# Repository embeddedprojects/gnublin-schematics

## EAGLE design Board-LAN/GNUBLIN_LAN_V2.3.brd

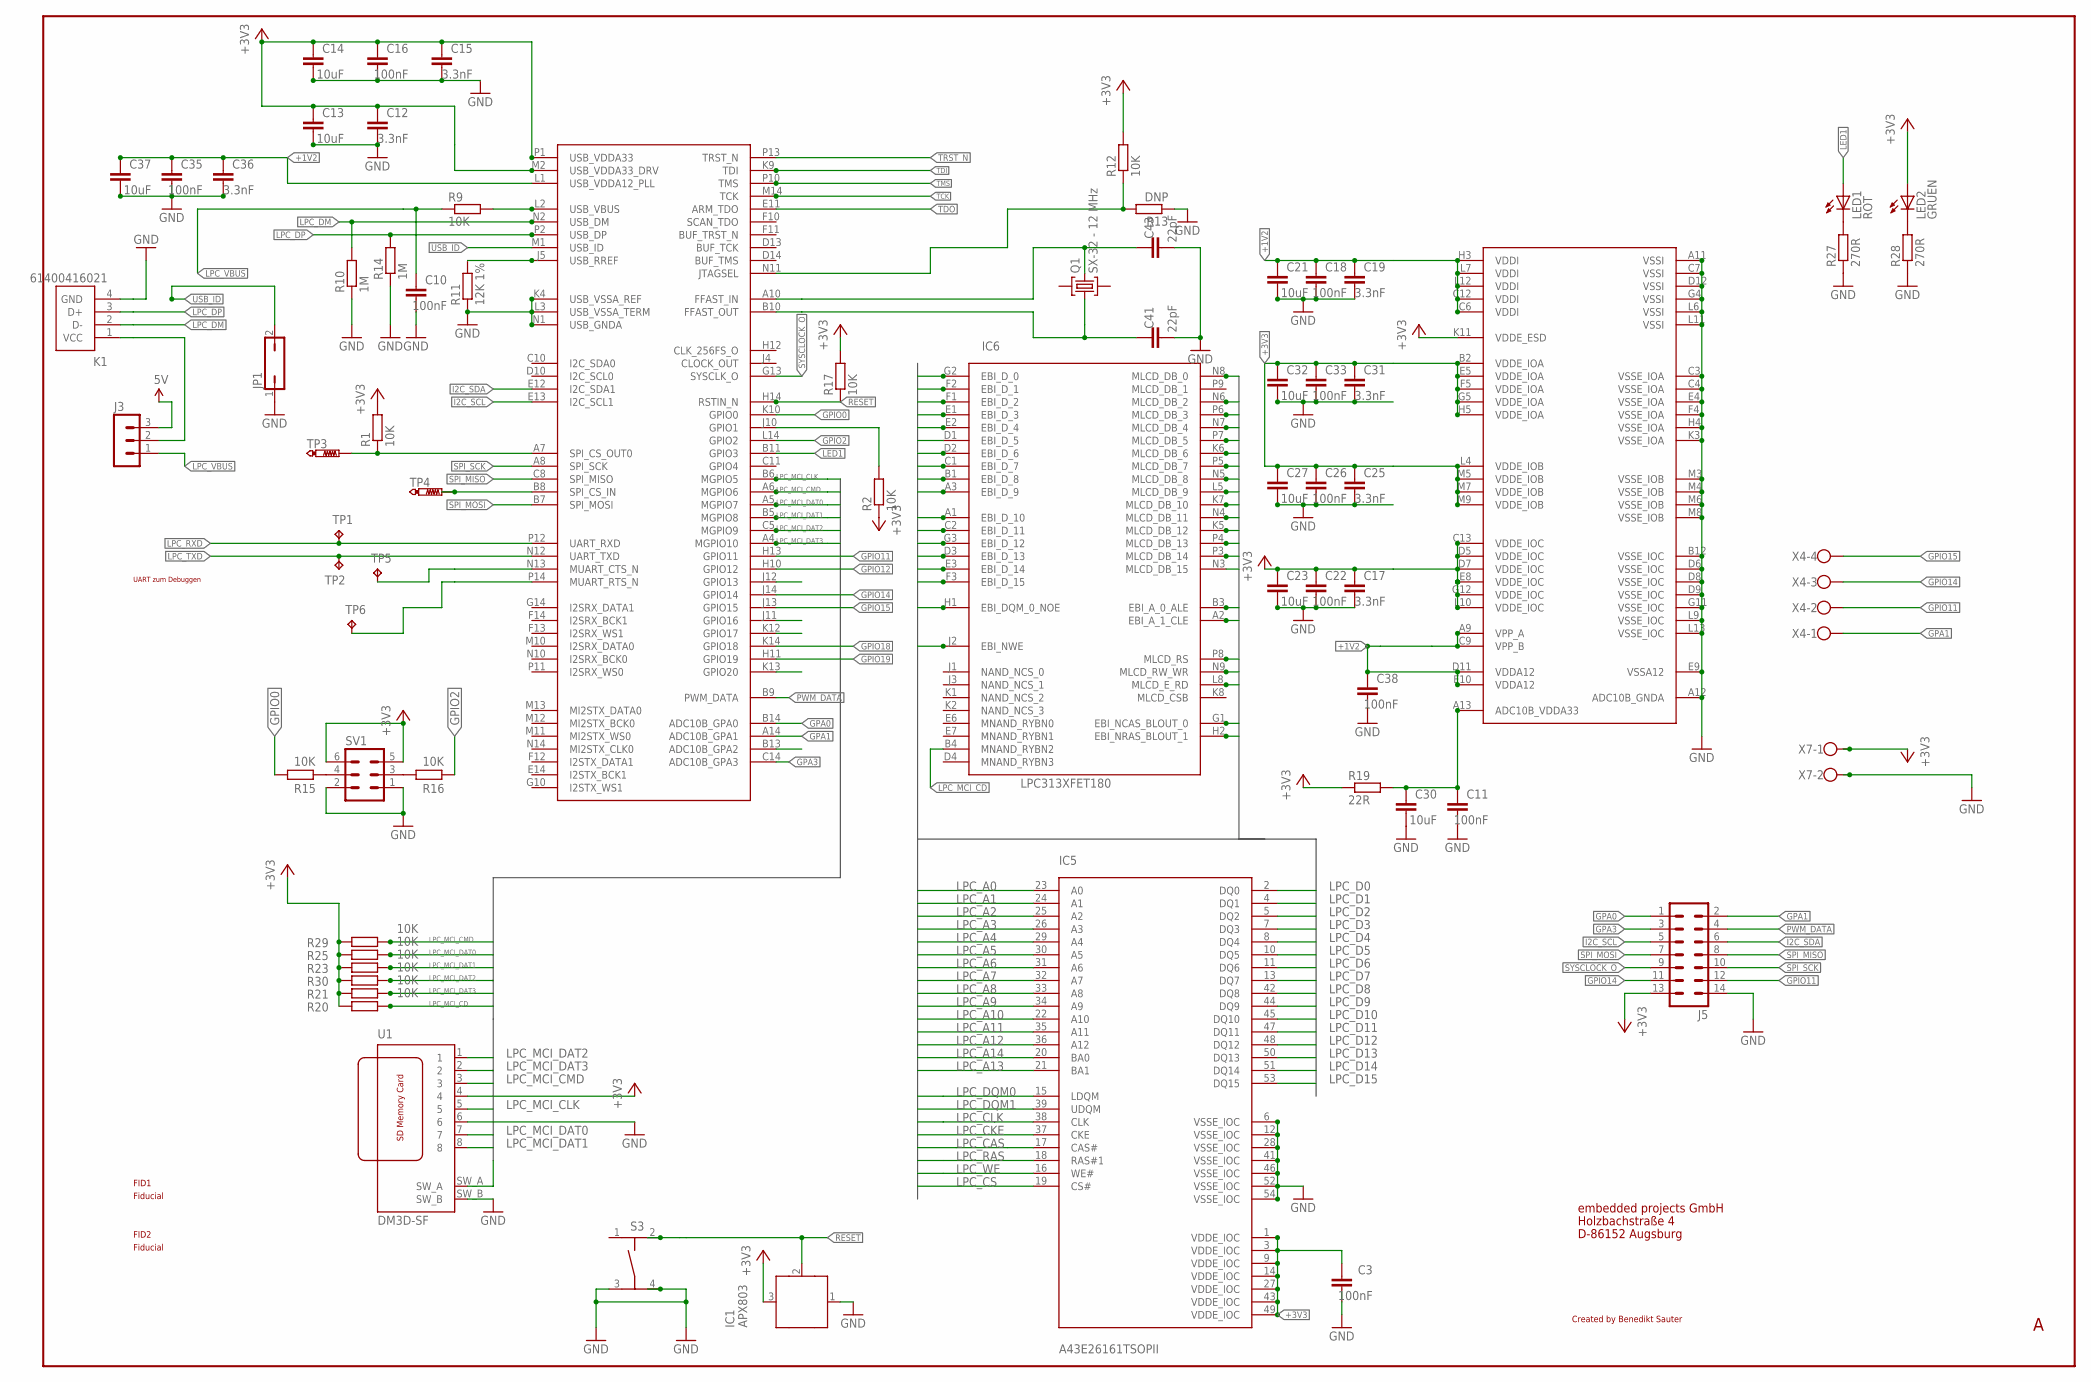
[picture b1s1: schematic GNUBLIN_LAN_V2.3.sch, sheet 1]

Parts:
C3, C10, C11, C16, C18, C22, C26, C33, C35, C38: 100nF; C0805
C12, C15, C17, C19, C25, C31, C36: 3.3nF; C0805
C13, C14, C21, C23, C27, C30, C32, C37: 10uF; C0805
C41, C43: 22pF; C0805
FID1, FID2: PASSERMARKEN_FIDUCIAL
IC1: APX803; SOT23
IC5: A43E26161TSOPII; TSOPII
IC6: LPC313XFET180; TFBGA180
J3: MA03-1
J5: ML14
JP1: JP1Q; JP1
K1: 61400416021
LED1: ROT; CHIP-LED0805
LED2: GRUEN; CHIP-LED0805
Q1: SX-32 - 12 MHz; SX-32; FARNELL 1712841
R1, R2, R9, R12, R15, R16, R17, R20, R21, R23, R25, R29, R30: 10K; R0805
R10, R14: 1M; R0805
R11: 12K 1%; R0805
R13: DNP; R0805
R19: 22R; R0805
R27, R28: 270R; R0805
S3: TASTER-9314_SMD
SV1: MA03-2
TP1, TP2: TPTP15R; TP15R
TP3, TP4: PTR1TP08R; TP08R
TP5, TP6: TPTP08R; TP08R
U1: DM3D-SF
X4: W237-04P; W237-4P
X7: W237-02P; W237-132

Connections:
5V: J3.3; also elsewhere on the board
+1V2: C18.2, C19.2, C21.2, C35.2, C36.2, C37.2, C38.2, IC6.A9 (VPP_A), IC6.C6 (VDDI), IC6.C9 (VPP_B), IC6.C12 (VDDI), IC6.D11 (VDDA12), IC6.E10 (VDDA12), IC6.H3 (VDDI), IC6.L1 (USB_VDDA12_PLL), IC6.L7 (VDDI), IC6.L12 (VDDI); also elsewhere on the board
+3V3: C3.2, C12.2, C13.2, C14.2, C15.2, C16.2, C17.2, C22.2, C23.2, C25.2, C26.2, C27.2, C31.2, C32.2, C33.2, IC1.3 (VCC), IC5.1 (VDDE_IOC), IC5.3 (VDDE_IOC), IC5.9 (VDDE_IOC), IC5.14 (VDDE_IOC), IC5.27 (VDDE_IOC), IC5.43 (VDDE_IOC), IC5.49 (VDDE_IOC), IC6.B2 (VDDE_IOA), IC6.C13 (VDDE_IOC), IC6.D5 (VDDE_IOC), IC6.D7 (VDDE_IOC), IC6.E5 (VDDE_IOA), IC6.E8 (VDDE_IOC), IC6.F5 (VDDE_IOA), IC6.G5 (VDDE_IOA), IC6.G12 (VDDE_IOC), IC6.H5 (VDDE_IOA), IC6.K11 (VDDE_ESD), IC6.L4 (VDDE_IOB), IC6.L10 (VDDE_IOC), IC6.M2 (USB_VDDA33_DRV), IC6.M5 (VDDE_IOB), IC6.M7 (VDDE_IOB), IC6.M9 (VDDE_IOB), IC6.P1 (USB_VDDA33), J5.13, LED2.A, R1.2, R2.1, R12.2, R17.2, R19.1, R20.1, R21.1, R23.1, R25.1, R29.1, R30.1, SV1.5, SV1.6, U1.4, X7.1; also elsewhere on the board
GND: C3.1, C10.1, C11.1, C12.1, C13.1, C14.1, C15.1, C16.1, C17.1, C18.1, C19.1, C21.1, C22.1, C23.1, C25.1, C26.1, C27.1, C30.1, C31.1, C32.1, C33.1, C35.1, C36.1, C37.1, C38.1, C41.1, C43.1, IC1.1 (GND), IC5.6 (VSSE_IOC), IC5.12 (VSSE_IOC), IC5.28 (VSSE_IOC), IC5.41 (VSSE_IOC), IC5.46 (VSSE_IOC), IC5.52 (VSSE_IOC), IC5.54 (VSSE_IOC), IC6.A11 (VSSI), IC6.A12 (ADC10B_GNDA), IC6.B12 (VSSE_IOC), IC6.C3 (VSSE_IOA), IC6.C4 (VSSE_IOA), IC6.C7 (VSSI), IC6.D6 (VSSE_IOC), IC6.D8 (VSSE_IOC), IC6.D9 (VSSE_IOC), IC6.D12 (VSSI), IC6.E4 (VSSE_IOA), IC6.E9 (VSSA12), IC6.F4 (VSSE_IOA), IC6.G4 (VSSI), IC6.G11 (VSSE_IOC), IC6.H4 (VSSE_IOA), IC6.K3 (VSSE_IOA), IC6.K4 (USB_VSSA_REF), IC6.L3 (USB_VSSA_TERM), IC6.L6 (VSSI), IC6.L9 (VSSE_IOC), IC6.L11 (VSSI), IC6.L13 (VSSE_IOC), IC6.M3 (VSSE_IOB), IC6.M4 (VSSE_IOB), IC6.M6 (VSSE_IOB), IC6.M8 (VSSE_IOB), IC6.N1 (USB_GNDA), J5.14, JP1.1, K1.4 (GND), R10.1, R11.1, R13.1, R14.1, R27.1, R28.1, S3.3, S3.4, SV1.1, SV1.2, U1.6, U1.SW_B, X7.2; also elsewhere on the board
GPA0: IC6.B14 (ADC10B_GPA0), J5.1
GPA1: IC6.A14 (ADC10B_GPA1), J5.2, X4.1
GPA3: IC6.C14 (ADC10B_GPA3), J5.3
GPIO0: IC6.K10 (GPIO0), R15.1
GPIO2: IC6.L14 (GPIO2), R16.2
GPIO11: IC6.H13 (GPIO11), J5.12, X4.2
GPIO12: IC6.H10 (GPIO12); also elsewhere on the board
GPIO14: IC6.J14 (GPIO14), J5.11, X4.3
GPIO15: IC6.J13 (GPIO15), X4.4
GPIO18: IC6.K14 (GPIO18); also elsewhere on the board
GPIO19: IC6.H11 (GPIO19); also elsewhere on the board
I2C_SCL: IC6.E13 (I2C_SCL1), J5.5; also elsewhere on the board
I2C_SDA: IC6.E12 (I2C_SDA1), J5.6; also elsewhere on the board
LED1: IC6.B11 (GPIO3), LED1.A
LPC_A0: IC5.23 (A0), IC6.B3 (EBI_A_0_ALE)
LPC_A1: IC5.24 (A1), IC6.A2 (EBI_A_1_CLE)
LPC_A2: IC5.25 (A2), IC6.N6 (MLCD_DB_2)
LPC_A3: IC5.26 (A3), IC6.P6 (MLCD_DB_3)
LPC_A4: IC5.29 (A4), IC6.N7 (MLCD_DB_4)
LPC_A5: IC5.30 (A5), IC6.P7 (MLCD_DB_5)
LPC_A6: IC5.31 (A6), IC6.K6 (MLCD_DB_6)
LPC_A7: IC5.32 (A7), IC6.P5 (MLCD_DB_7)
LPC_A8: IC5.33 (A8), IC6.N5 (MLCD_DB_8)
LPC_A9: IC5.34 (A9), IC6.L5 (MLCD_DB_9)
LPC_A10: IC5.22 (A10), IC6.K7 (MLCD_DB_10)
LPC_A11: IC5.35 (A11), IC6.N4 (MLCD_DB_11)
LPC_A12: IC5.36 (A12), IC6.K5 (MLCD_DB_12)
LPC_A13: IC5.21 (BA1), IC6.P4 (MLCD_DB_13)
LPC_A14: IC5.20 (BA0), IC6.P3 (MLCD_DB_14)
LPC_A15: IC6.N3 (MLCD_DB_15)
LPC_CAS: IC5.17 (CAS#), IC6.G1 (EBI_NCAS_BLOUT_0)
LPC_CKE: IC5.37 (CKE), IC6.L8 (MLCD_E_RD)
LPC_CLK: IC5.38 (CLK), IC6.N8 (MLCD_DB_0)
LPC_CS: IC5.19 (CS#), IC6.P8 (MLCD_RS)
LPC_D0: IC5.2 (DQ0), IC6.G2 (EBI_D_0)
LPC_D1: IC5.4 (DQ1), IC6.F2 (EBI_D_1)
LPC_D2: IC5.5 (DQ2), IC6.F1 (EBI_D_2)
LPC_D3: IC5.7 (DQ3), IC6.E1 (EBI_D_3)
LPC_D4: IC5.8 (DQ4), IC6.E2 (EBI_D_4)
LPC_D5: IC5.10 (DQ5), IC6.D1 (EBI_D_5)
LPC_D6: IC5.11 (DQ6), IC6.D2 (EBI_D_6)
LPC_D7: IC5.13 (DQ7), IC6.C1 (EBI_D_7)
LPC_D8: IC5.42 (DQ8), IC6.B1 (EBI_D_8)
LPC_D9: IC5.44 (DQ9), IC6.A3 (EBI_D_9)
LPC_D10: IC5.45 (DQ10), IC6.A1 (EBI_D_10)
LPC_D11: IC5.47 (DQ11), IC6.C2 (EBI_D_11)
LPC_D12: IC5.48 (DQ12), IC6.G3 (EBI_D_12)
LPC_D13: IC5.50 (DQ13), IC6.D3 (EBI_D_13)
LPC_D14: IC5.51 (DQ14), IC6.E3 (EBI_D_14)
LPC_D15: IC5.53 (DQ15), IC6.F3 (EBI_D_15)
LPC_DM: IC6.N2 (USB_DM), K1.2 (D-), R10.2
LPC_DP: IC6.P2 (USB_DP), K1.3 (D+), R14.2
LPC_DQM0: IC5.15 (LDQM), IC6.H1 (EBI_DQM_0_NOE)
LPC_DQM1: IC5.39 (UDQM), IC6.N9 (MLCD_RW_WR)
LPC_MCI_CD: IC6.B4 (MNAND_RYBN2), R20.2, U1.SW_A
LPC_MCI_CLK: IC6.B6 (MGPIO5), U1.5
LPC_MCI_CMD: IC6.A6 (MGPIO6), R29.2, U1.3
LPC_MCI_DAT0: IC6.A5 (MGPIO7), R25.2, U1.7
LPC_MCI_DAT1: IC6.B5 (MGPIO8), R23.2, U1.8
LPC_MCI_DAT2: IC6.C5 (MGPIO9), R30.2, U1.1
LPC_MCI_DAT3: IC6.A4 (MGPIO10), R21.2, U1.2
LPC_RAS: IC5.18 (RAS#1), IC6.H2 (EBI_NRAS_BLOUT_1)
LPC_RXD: IC6.P12 (UART_RXD), TP1.TP; also elsewhere on the board
LPC_TXD: IC6.N12 (UART_TXD), TP2.TP; also elsewhere on the board
LPC_VBUS: C10.2, J3.1, R9.1
LPC_WE: IC5.16 (WE#), IC6.J2 (EBI_NWE)
unnamed: LED1.C, R27.2
unnamed: LED2.C, R28.2
unnamed: IC6.N11 (JTAGSEL), R12.1, R13.2
unnamed: J3.2, K1.1 (VCC)
unnamed: IC6.A7 (SPI_CS_OUT0), R1.1, TP3.TP
unnamed: IC6.B8 (SPI_CS_IN), TP4.TP
unnamed: IC6.J10 (GPIO1), R2.2
unnamed: R15.2, SV1.4
unnamed: R16.1, SV1.3
unnamed: IC6.N13 (MUART_CTS_N), TP5.TP
unnamed: IC6.P14 (MUART_RTS_N), TP6.TP
unnamed: C11.2, C30.2, IC6.A13 (ADC10B_VDDA33), R19.2
unnamed: IC6.J5 (USB_RREF), R11.2
unnamed: IC6.L2 (USB_VBUS), R9.2
PWM_DATA: IC6.B9 (PWM_DATA), J5.4
RESET: IC1.2 (!RESET), IC6.H14 (RSTIN_N), R17.1, S3.2
SPI_MISO: IC6.C8 (SPI_MISO), J5.8; also elsewhere on the board
SPI_MOSI: IC6.B7 (SPI_MOSI), J5.7; also elsewhere on the board
SPI_SCK: IC6.A8 (SPI_SCK), J5.10; also elsewhere on the board
SYSCLOCK_O: IC6.G13 (SYSCLK_O), J5.9
TCK: IC6.M14 (TCK)
TDI: IC6.K9 (TDI)
TDO: IC6.E11 (ARM_TDO)
TMS: IC6.P10 (TMS)
TRST_N: IC6.P13 (TRST_N)
USB_ID: IC6.M1 (USB_ID), JP1.2
XTAL1: C43.2, IC6.A10 (FFAST_IN), Q1.3 (2)
XTAL2: C41.2, IC6.B10 (FFAST_OUT), Q1.1

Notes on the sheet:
embedded projects GmbH
Holzbachstraße 4
D-86152 Augsburg
Created by Benedikt Sauter
UART zum Debuggen

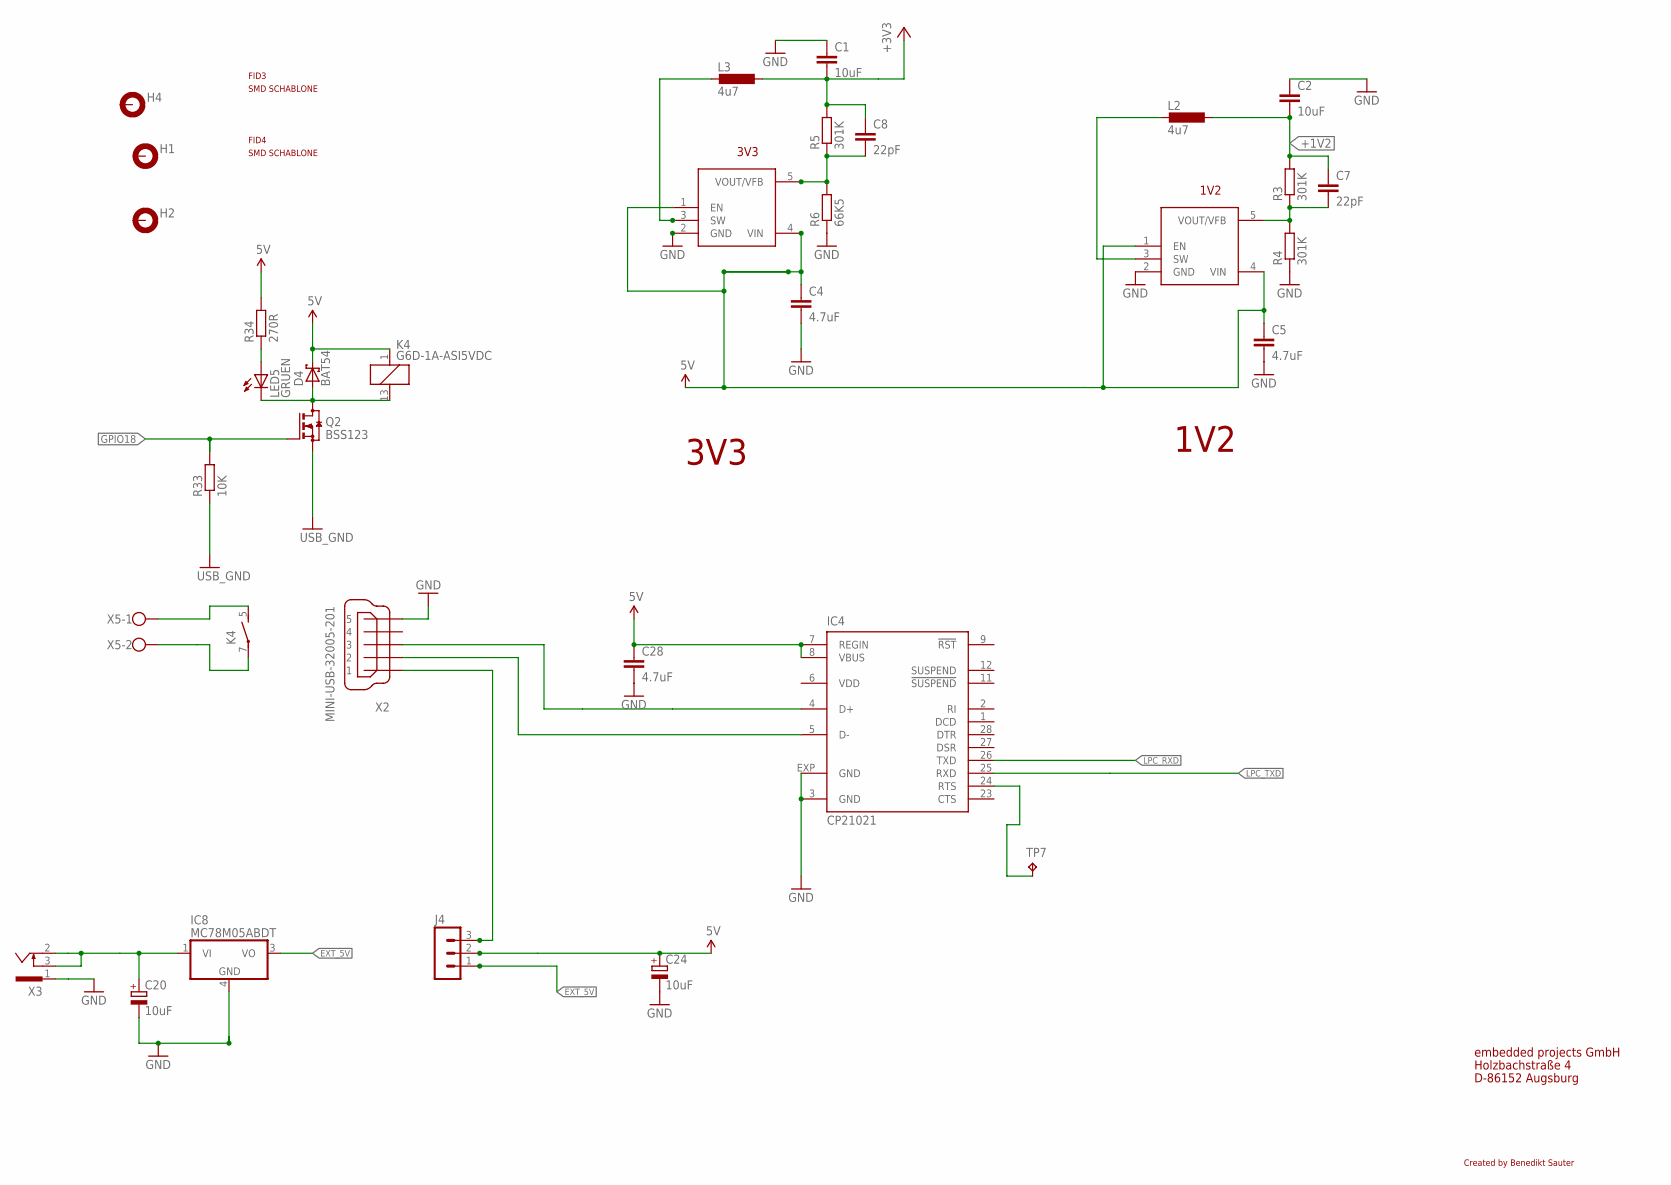
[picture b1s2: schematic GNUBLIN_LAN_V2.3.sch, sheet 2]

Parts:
C1, C2: 10uF; C0805
C4, C5, C28: 4.7uF; C0805
C7, C8: 22pF; C0805
C20, C24: 10uF; D/7343-31R
D4: BAT54; DIODE_SOT23
FID3, FID4: PASSERMARKEN_FIDUCIAL
H1, H2, H4: MOUNT-PAD-ROUND3.2; 3,2-PAD
IC2, IC3: AS1324; TSOT23
IC4: CP21021; MLP28
IC8: MC78M05ABDT; DPACK_3
J4: MA03-1
K4: G6D-1A-ASI5VDC; RELAY_G6D
L2, L3: 4u7; PSU3014
LED5: GRUEN; CHIP-LED0805
Q2: BSS123; TRANSISTOR-SMALL-SIGNAL_SOT23
R3, R4, R5: 301K; R0805
R6: 66K5; R0805
R33: 10K; R0805
R34: 270R; R0805
TP7: TPTP08R; TP08R
X2: MINI-USB-32005-201; 32005-201
X3: 733980-62
X5: W237-02P; W237-132

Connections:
5V: C4.1, C5.1, C24.+, C28.1, D4.3 (C), IC2.1 (EN), IC2.4 (VIN), IC3.1 (EN), IC3.4 (VIN), IC4.7 (REGIN), IC4.8 (VBUS), J4.2, K4.1, R34.2; also elsewhere on the board
+1V2: C2.2, C7.1, L2.2, R3.2; also elsewhere on the board
+3V3: C1.2, C8.1, L3.2, R5.2; also elsewhere on the board
D+: IC4.4 (D+), X2.3
D-: IC4.5 (D-), X2.2
EXT_5V: IC8.3 (VO), J4.1
GND: C1.1, C2.1, C4.2, C5.2, C20.-, C24.-, C28.2, IC2.2 (GND), IC3.2 (GND), IC4.3 (GND), IC4.EXP (GND), IC8.4 (GND), Q2.2 (S), R4.1, R6.1, R33.1, X2.5, X3.1; also elsewhere on the board
GPIO18: Q2.1 (G), R33.2; also elsewhere on the board
LPC_RXD: IC4.26 (TXD); also elsewhere on the board
LPC_TXD: IC4.25 (RXD); also elsewhere on the board
unnamed: IC2.3 (SW), L2.1
unnamed: J4.3, X2.1
unnamed: IC4.24 (RTS), TP7.TP
unnamed: D4.1 (A), K4.13 (2), LED5.C, Q2.3 (D)
unnamed: C7.2, IC2.5 (VOUT/VFB), R3.1, R4.2
unnamed: LED5.A, R34.1
unnamed: K4.5 (S), X5.1
unnamed: IC3.3 (SW), L3.1
unnamed: C20.+, IC8.1 (VI), X3.2, X3.3
unnamed: C8.2, IC3.5 (VOUT/VFB), R5.1, R6.2
RIGHT: K4.7, X5.2
VDD: IC4.6 (VDD)

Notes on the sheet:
Created by Benedikt Sauter
3V3
1V2
embedded projects GmbH
Holzbachstraße 4
D-86152 Augsburg

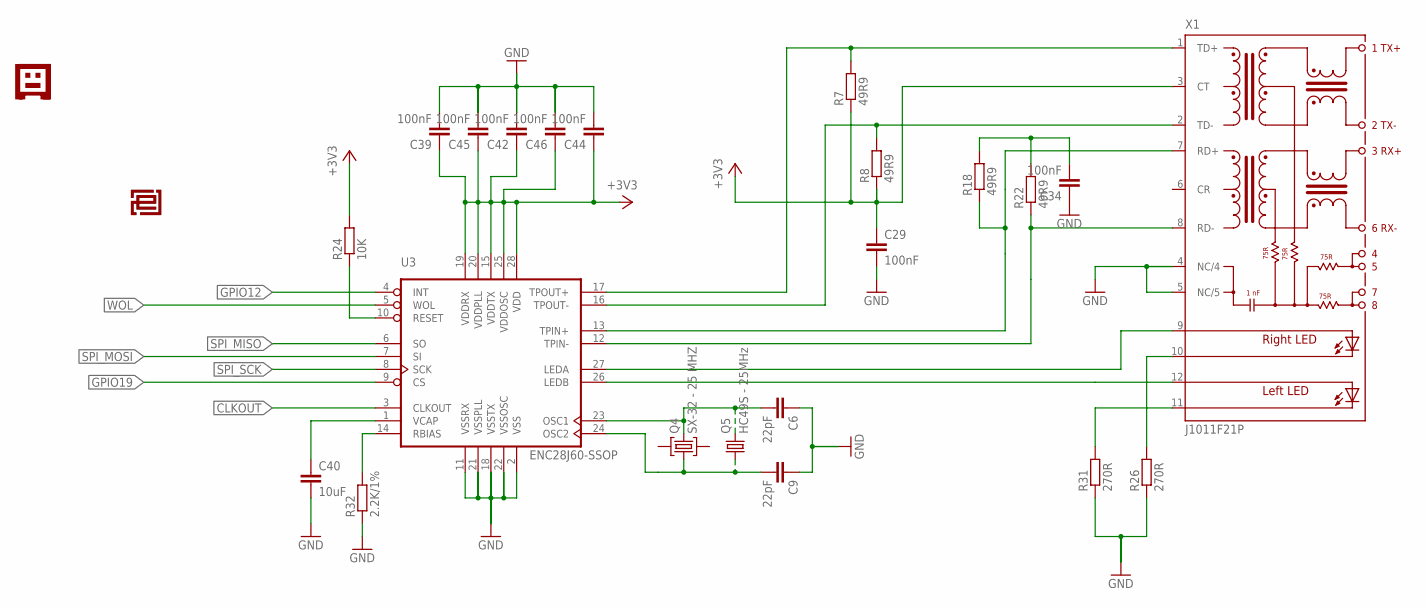
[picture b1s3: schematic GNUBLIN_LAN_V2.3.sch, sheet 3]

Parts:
C6, C9: 22pF; C0805
C29, C34, C39, C42, C44, C45, C46: 100nF; C0805
C40: 10uF; C0805
Q4: SX-32 - 25 MHZ; SX-32; FARNELL 1712841
Q5: HC49S - 25MHz; HC49/S
R7, R8, R18, R22: 49R9; R0805
R24: 10K; R0805
R26, R31: 270R; R0805
R32: 2.2K/1%; R0805
U3: ENC28J60-SSOP; SSOP28; FARNELL 1084620
U$3: EPLOGOSIEB; EPLOGOSIEBDRUCK
U$7: GNUBLINLOGOSIEB; GNUSIEBDRUCK
X1: J1011F21P; J1

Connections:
+3V3: C29.1, C39.1, C42.1, C44.1, C45.1, C46.1, R7.1, R8.1, R24.2, U3.15 (VDDTX), U3.19 (VDDRX), U3.20 (VDDPLL), U3.25 (VDDOSC), U3.28 (VDD), X1.3 (CT); also elsewhere on the board
CLKOUT: U3.3 (CLKOUT)
GND: C6.1, C9.1, C29.2, C34.1, C39.2, C40.2, C42.2, C44.2, C45.2, C46.2, R26.1, R31.1, R32.1, U3.2 (VSS), U3.11 (VSSRX), U3.18 (VSSTX), U3.21 (VSSPLL), U3.22 (VSSOSC), X1.4 (NC/4), X1.5 (NC/5); also elsewhere on the board
GPIO12: U3.4 (INT); also elsewhere on the board
GPIO19: U3.9 (CS); also elsewhere on the board
LINKACT: R26.2, X1.10 (C-R)
unnamed: C34.2, R18.2, R22.2
unnamed: R24.1, U3.10 (RESET)
unnamed: C40.1, U3.1 (VCAP)
unnamed: U3.27 (LEDA), X1.9 (A-R)
unnamed: R32.2, U3.14 (RBIAS)
unnamed: U3.26 (LEDB), X1.12 (AL)
RX+: R18.1, U3.13 (TPIN+), X1.7 (RD+)
RX-: R22.1, U3.12 (TPIN-), X1.8 (RD-)
SPEED: R31.2, X1.11 (C-L)
SPI_MISO: U3.6 (SO); also elsewhere on the board
SPI_MOSI: U3.7 (SI); also elsewhere on the board
SPI_SCK: U3.8 (SCK); also elsewhere on the board
TX+: R7.2, U3.17 (TPOUT+), X1.1 (TD+)
TX-: R8.2, U3.16 (TPOUT-), X1.2 (TD-)
WOL: U3.5 (WOL)
XT1: C9.2, Q4.1, Q5.1, U3.24 (OSC2)
XT2: C6.2, Q4.3 (2), Q5.2, U3.23 (OSC1)

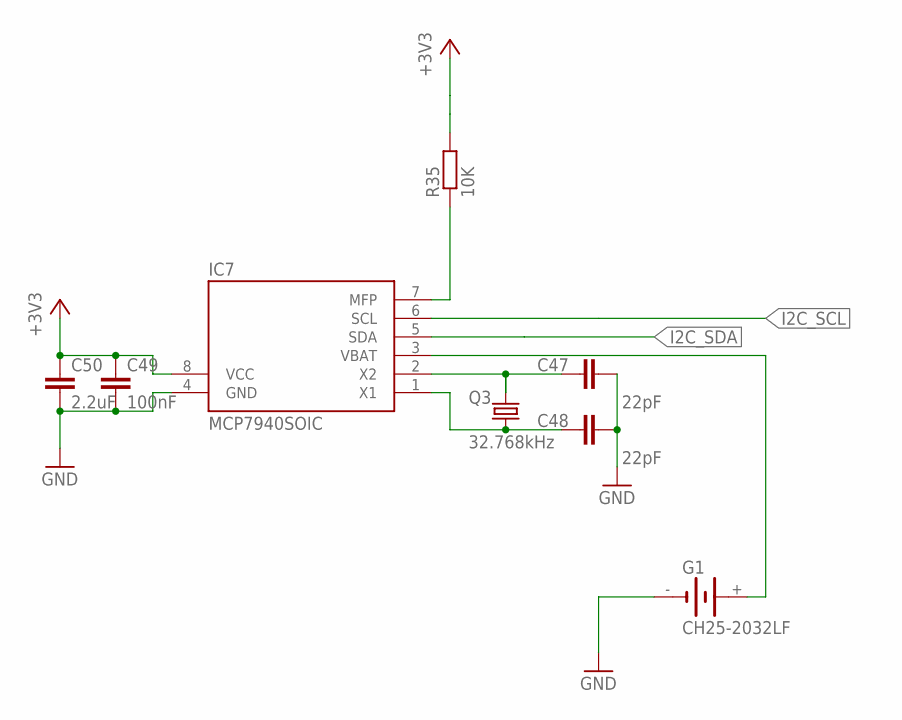
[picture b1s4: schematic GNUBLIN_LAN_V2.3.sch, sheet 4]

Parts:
C47, C48: 22pF; C0805
C49: 100nF; C0805
C50: 2.2uF; C0805
G1: CH25-2032LF; CH25
IC7: MCP7940SOIC; SOIC-8; FARNELL 2098890
Q3: 32.768kHz; TC26H
R35: 10K; R0805

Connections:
+3V3: C49.1, C50.1, IC7.8 (VCC), R35.2; also elsewhere on the board
GND: C47.2, C48.2, C49.2, C50.2, G1.-, IC7.4 (GND); also elsewhere on the board
I2C_SCL: IC7.6 (SCL); also elsewhere on the board
I2C_SDA: IC7.5 (SDA); also elsewhere on the board
unnamed: IC7.7 (MFP), R35.1
unnamed: C48.1, IC7.1 (X1), Q3.2
unnamed: C47.1, IC7.2 (X2), Q3.1
VBAT: G1.+, IC7.3 (VBAT)

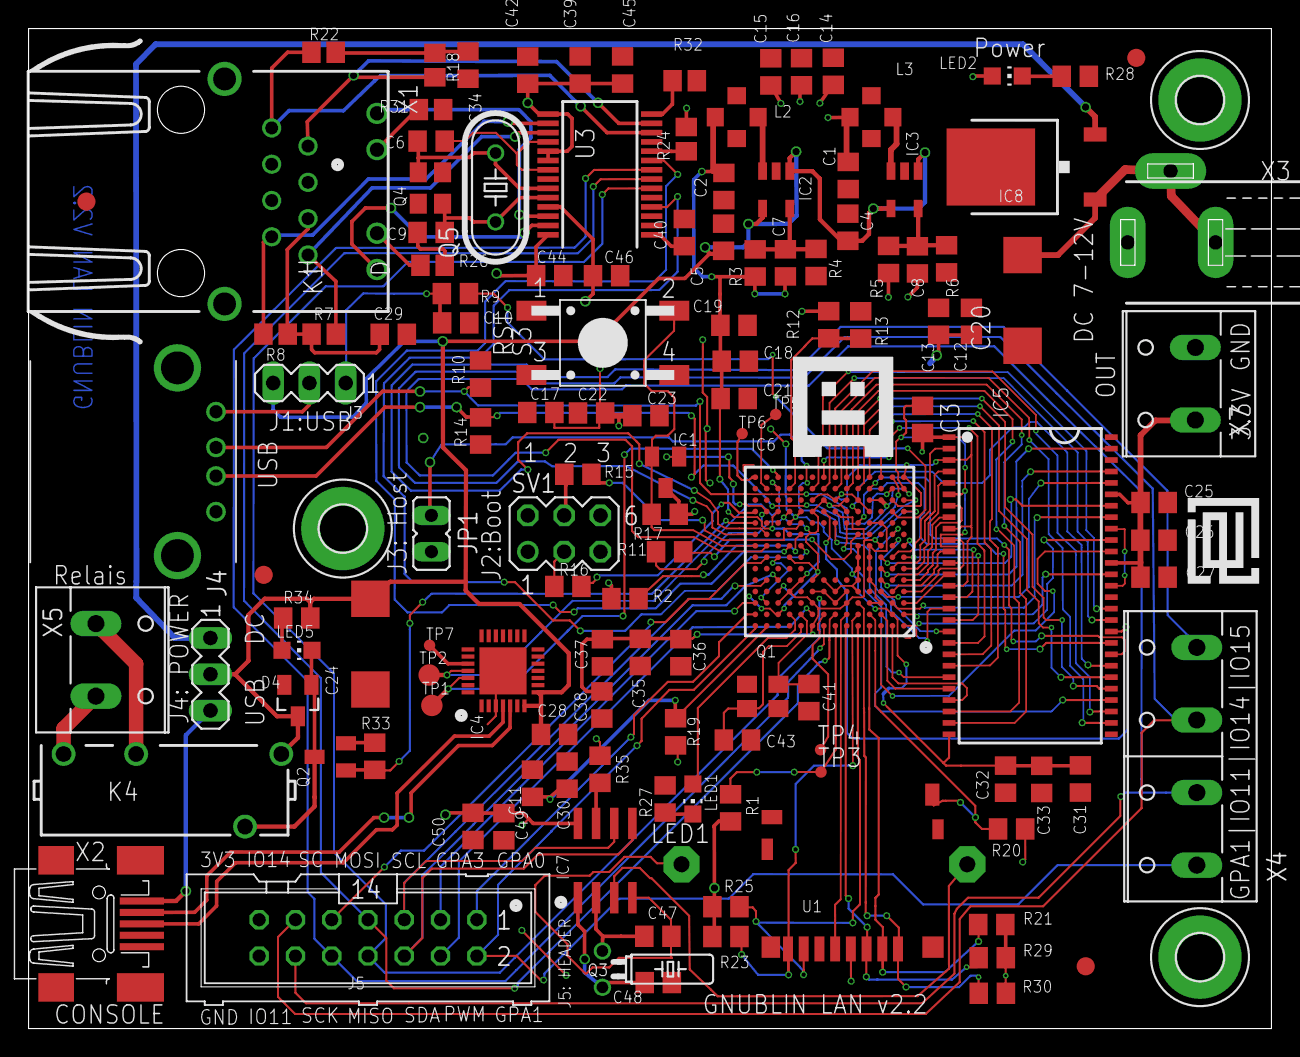
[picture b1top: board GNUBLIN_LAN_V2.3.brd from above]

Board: 2 copper layers, 87.0 x 70.0 mm, 137 parts (1 on the bottom side), 124 nets.

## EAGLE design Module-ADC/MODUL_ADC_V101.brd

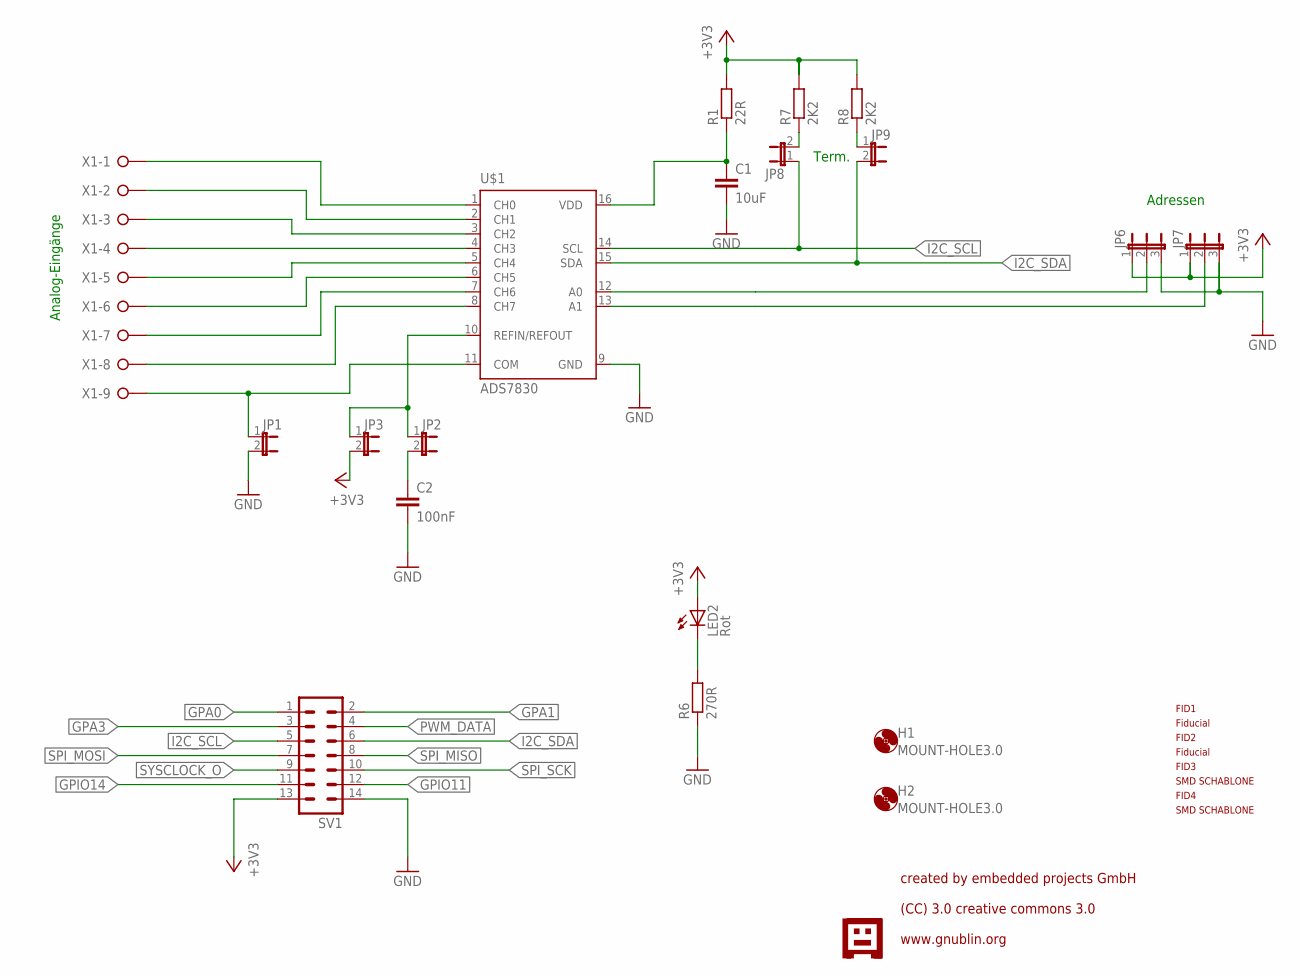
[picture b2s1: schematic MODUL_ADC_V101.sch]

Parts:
C1: 10uF; C0805
C2: 100nF; C0805
FID1, FID2, FID3, FID4: PASSERMARKEN_FIDUCIAL
H1, H2: MOUNT-HOLE3.0; 3,0
JP1, JP2, JP3, JP8, JP9: JP1E; JP1
JP6, JP7: JP2E; JP2
LED2: Rot; CHIP-LED0805
R1: 22R; R0805
R6: 270R; R0805
R7, R8: 2K2; R0805
SV1: ML14
U$1: ADS7830; TSSOP16; FARNELL 1180129
U$2: GNUBLINLOGOSIEB; GNUSIEBDRUCK
X1: W237-09P; W237-9P

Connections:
+3V3: JP3.2, JP6.1, JP7.1, LED2.A, R1.2, R7.2, R8.2, SV1.13
A0: JP6.2, U$1.12 (A0)
A1: JP7.2, U$1.13 (A1)
GND: C1.2, C2.2, JP1.2, JP6.3, JP7.3, R6.1, SV1.14, U$1.9 (GND)
GPA0: SV1.1
GPA1: SV1.2
GPA3: SV1.3
GPIO11: SV1.12
GPIO14: SV1.11
I2C_SCL: JP8.1, SV1.5, U$1.14 (SCL)
I2C_SDA: JP9.2, SV1.6, U$1.15 (SDA)
unnamed: C1.1, R1.1, U$1.16 (VDD)
unnamed: JP2.1, JP3.1, U$1.10 (REFIN/REFOUT)
unnamed: U$1.1 (CH0), X1.1
unnamed: U$1.2 (CH1), X1.2
unnamed: U$1.3 (CH2), X1.3
unnamed: U$1.4 (CH3), X1.4
unnamed: U$1.5 (CH4), X1.5
unnamed: U$1.6 (CH5), X1.6
unnamed: LED2.C, R6.2
unnamed: U$1.7 (CH6), X1.7
unnamed: U$1.8 (CH7), X1.8
unnamed: JP1.1, U$1.11 (COM), X1.9
unnamed: C2.1, JP2.2
unnamed: JP8.2, R7.1
unnamed: JP9.1, R8.1
PWM_DATA: SV1.4
SPI_MISO: SV1.8
SPI_MOSI: SV1.7
SPI_SCK: SV1.10
SYSCLOCK_O: SV1.9

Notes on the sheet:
Term.
Adressen
Analog-Eingänge
created by embedded projects GmbH (CC) 3.0 creative commons 3.0 www.gnublin.org

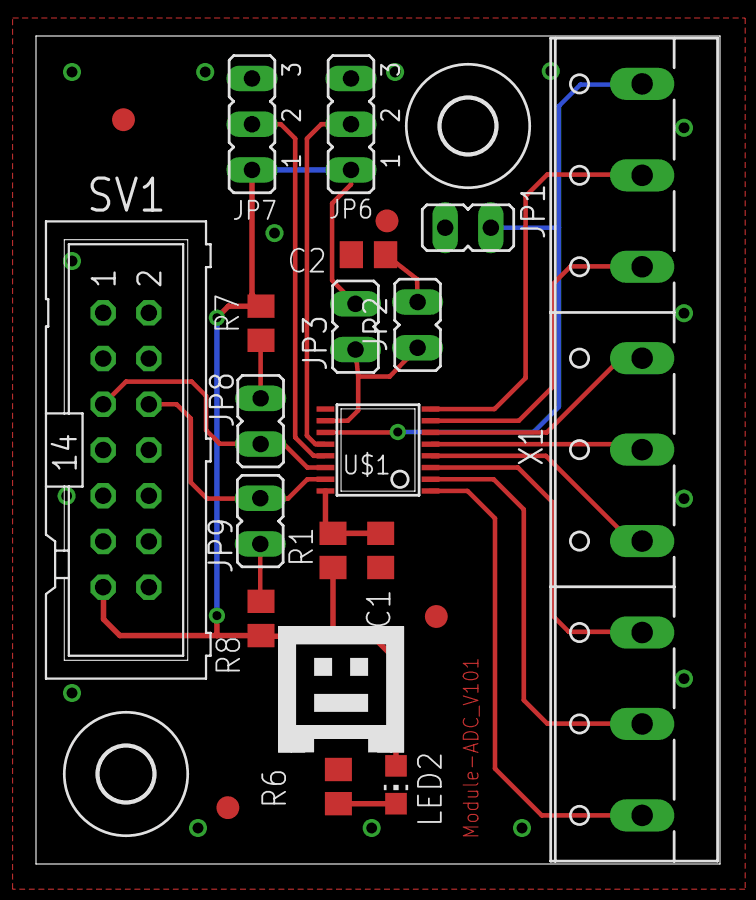
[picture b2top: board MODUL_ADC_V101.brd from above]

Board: 2 copper layers, 38.0 x 46.0 mm, 24 parts (0 on the bottom side), 21 nets.

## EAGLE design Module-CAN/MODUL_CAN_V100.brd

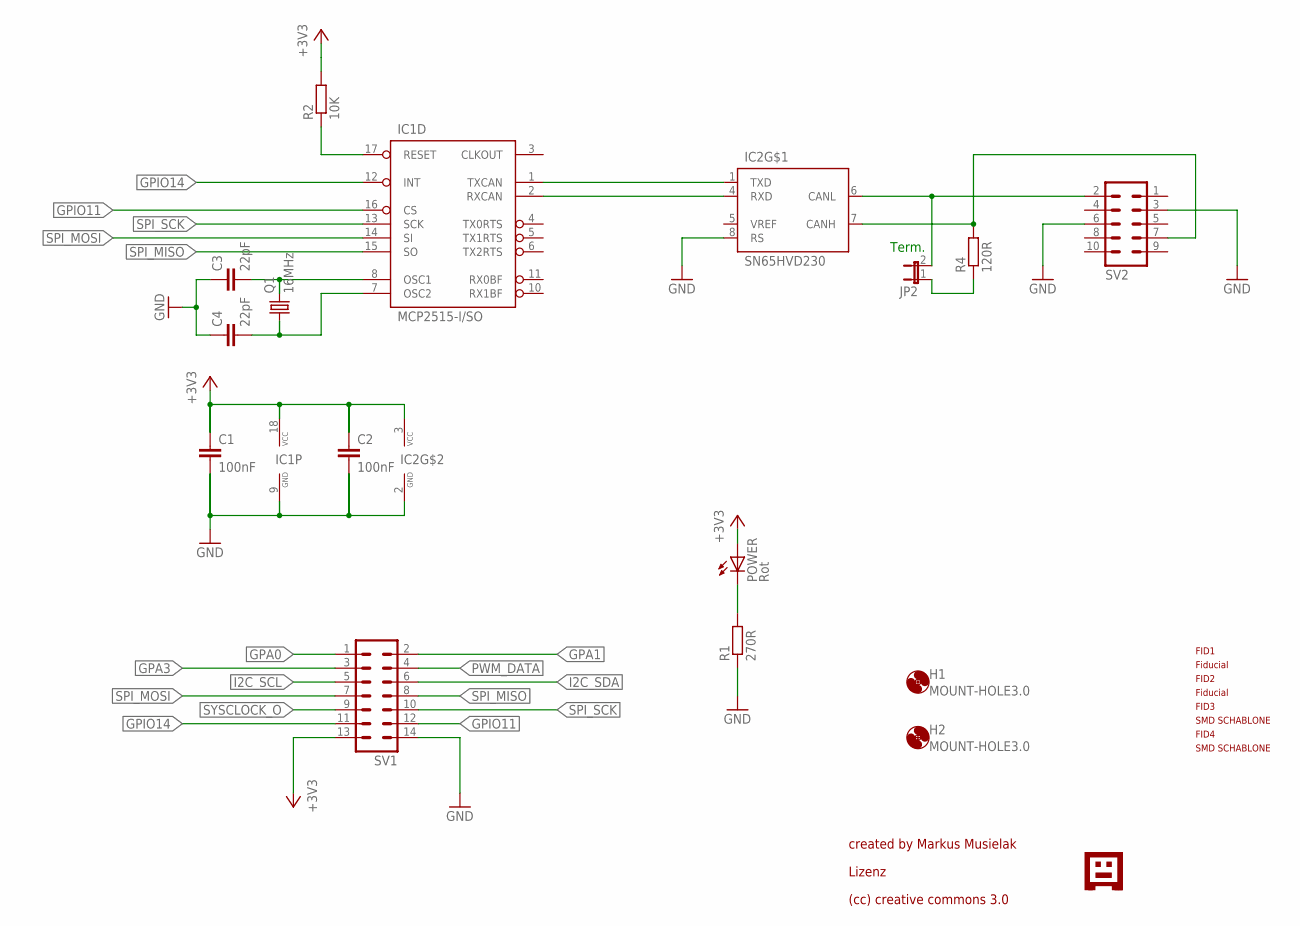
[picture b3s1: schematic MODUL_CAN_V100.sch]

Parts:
C1, C2: 100nF; C0805
C3, C4: 22pF; C0805
FID1, FID2, FID3, FID4: PASSERMARKEN_FIDUCIAL
H1, H2: MOUNT-HOLE3.0; 3,0
IC1: MCP2515-I/SO; SO-18W; FARNELL 1292239
IC2: SN65HVD230; SO08; FARNELL 1103105
JP2: JP1E; JP1
POWER: Rot; CHIP-LED0805
Q1: 16MHz; HC49UP
R1: 270R; R0805
R2: 10K; R0805
R4: 120R; R0805
SV1: ML14
SV2: ML10
U$2: GNUBLINLOGOSIEB; GNUSIEBDRUCK

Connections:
+3V3: C1.1, C2.1, IC1.18 (VCC), IC2.3 (VCC), POWER.A, R2.2, SV1.13
CANH: IC2.7 (CANH), R4.2, SV2.7
CANL: IC2.6 (CANL), JP2.2, SV2.2
GND: C1.2, C2.2, C3.1, C4.1, IC1.9 (GND), IC2.2 (GND), IC2.8 (RS), R1.1, SV1.14, SV2.3, SV2.6
GPA0: SV1.1
GPA1: SV1.2
GPA3: SV1.3
GPIO11: IC1.16 (CS), SV1.12
GPIO14: IC1.12 (INT), SV1.11
I2C_SCL: SV1.5
I2C_SDA: SV1.6
unnamed: C3.2, IC1.8 (OSC1), Q1.2
unnamed: C4.2, IC1.7 (OSC2), Q1.1
unnamed: IC1.1 (TXCAN), IC2.1 (TXD)
unnamed: IC1.2 (RXCAN), IC2.4 (RXD)
unnamed: IC1.17 (RESET), R2.1
unnamed: POWER.C, R1.2
unnamed: JP2.1, R4.1
PWM_DATA: SV1.4
SPI_MISO: IC1.15 (SO), SV1.8
SPI_MOSI: IC1.14 (SI), SV1.7
SPI_SCK: IC1.13 (SCK), SV1.10
SYSCLOCK_O: SV1.9

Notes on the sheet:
created by Markus Musielak
Term.
Lizenz
(cc) creative commons 3.0

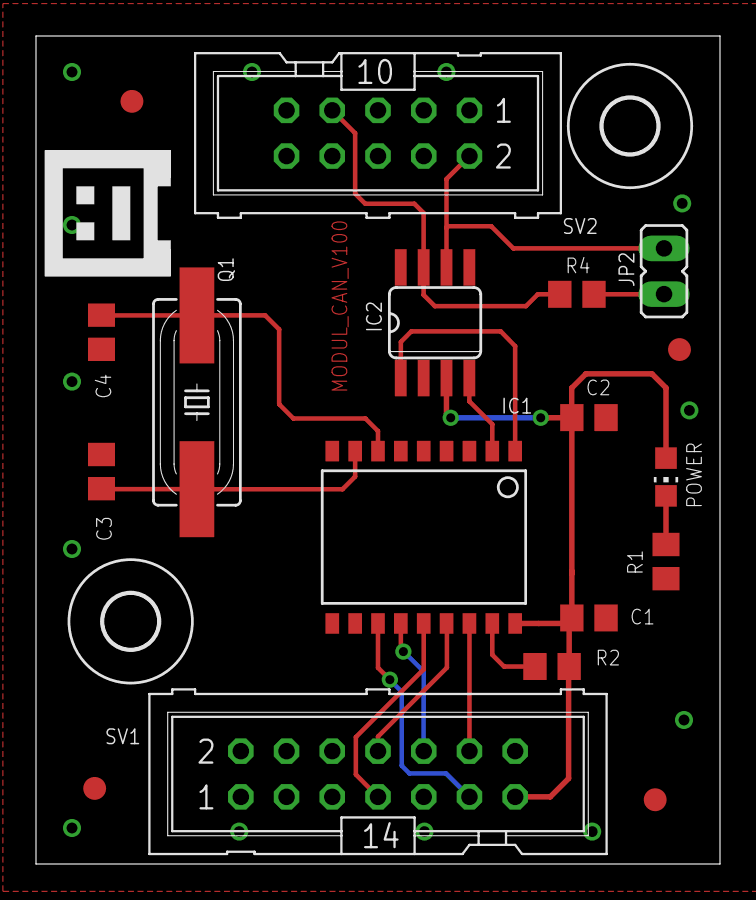
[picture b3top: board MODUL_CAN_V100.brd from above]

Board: 2 copper layers, 38.0 x 46.0 mm, 21 parts (0 on the bottom side), 16 nets.

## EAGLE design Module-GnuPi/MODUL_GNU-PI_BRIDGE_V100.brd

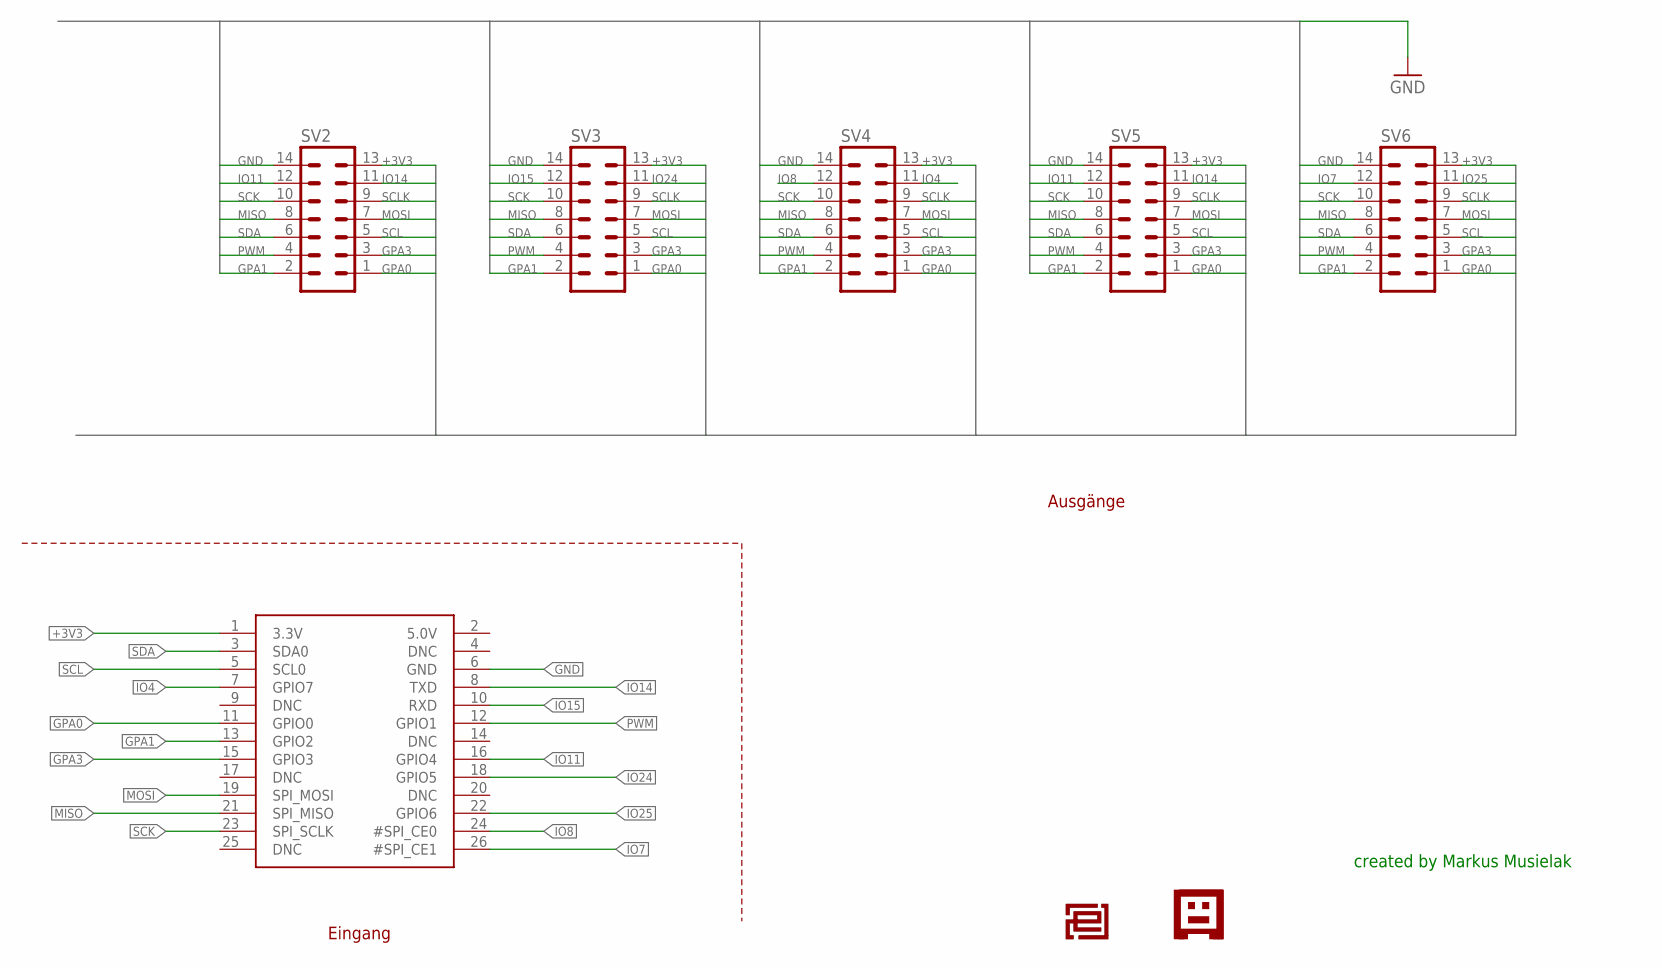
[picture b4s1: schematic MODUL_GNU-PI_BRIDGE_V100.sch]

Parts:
SV2, SV3, SV4, SV5, SV6: ML14
U$1: RASPBERRYPI_BB; RASBERRYPI_SHIELD
U$2: EPLOGOSIEB; EPLOGOSIEBDRUCK
U$4: GNUBLINLOGOSIEB; GNUSIEBDRUCK

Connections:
+3V3: SV2.13, SV3.13, SV4.13, SV5.13, SV6.13, U$1.1 (3.3V)
GND: SV2.14, SV3.14, SV4.14, SV5.14, SV6.14, U$1.6 (GND)
GPA0: SV2.1, SV3.1, SV4.1, SV5.1, SV6.1, U$1.11 (GPIO0)
GPA1: SV2.2, SV3.2, SV4.2, SV5.2, SV6.2, U$1.13 (GPIO2)
GPA3: SV2.3, SV3.3, SV4.3, SV5.3, SV6.3, U$1.15 (GPIO3)
IO4: SV4.11, U$1.7 (GPIO7)
IO7: SV6.12, U$1.26 (#SPI_CE1)
IO8: SV4.12, U$1.24 (#SPI_CE0)
IO11: SV2.12, SV5.12, U$1.16 (GPIO4)
IO14: SV2.11, SV5.11, U$1.8 (TXD)
IO15: SV3.12, U$1.10 (RXD)
IO24: SV3.11, U$1.18 (GPIO5)
IO25: SV6.11, U$1.22 (GPIO6)
MISO: SV2.8, SV3.8, SV4.8, SV5.8, SV6.8, U$1.21 (SPI_MISO)
MOSI: SV2.7, SV3.7, SV4.7, SV5.7, SV6.7, U$1.19 (SPI_MOSI)
PWM: SV2.4, SV3.4, SV4.4, SV5.4, SV6.4, U$1.12 (GPIO1)
SCK: SV2.10, SV3.10, SV4.10, SV5.10, SV6.10, U$1.23 (SPI_SCLK)
SCL: SV2.5, SV3.5, SV4.5, SV5.5, SV6.5, U$1.5 (SCL0)
SCLK: SV2.9, SV3.9, SV4.9, SV5.9, SV6.9
SDA: SV2.6, SV3.6, SV4.6, SV5.6, SV6.6, U$1.3 (SDA0)

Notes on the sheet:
created by Markus Musielak
Eingang
Ausgänge
